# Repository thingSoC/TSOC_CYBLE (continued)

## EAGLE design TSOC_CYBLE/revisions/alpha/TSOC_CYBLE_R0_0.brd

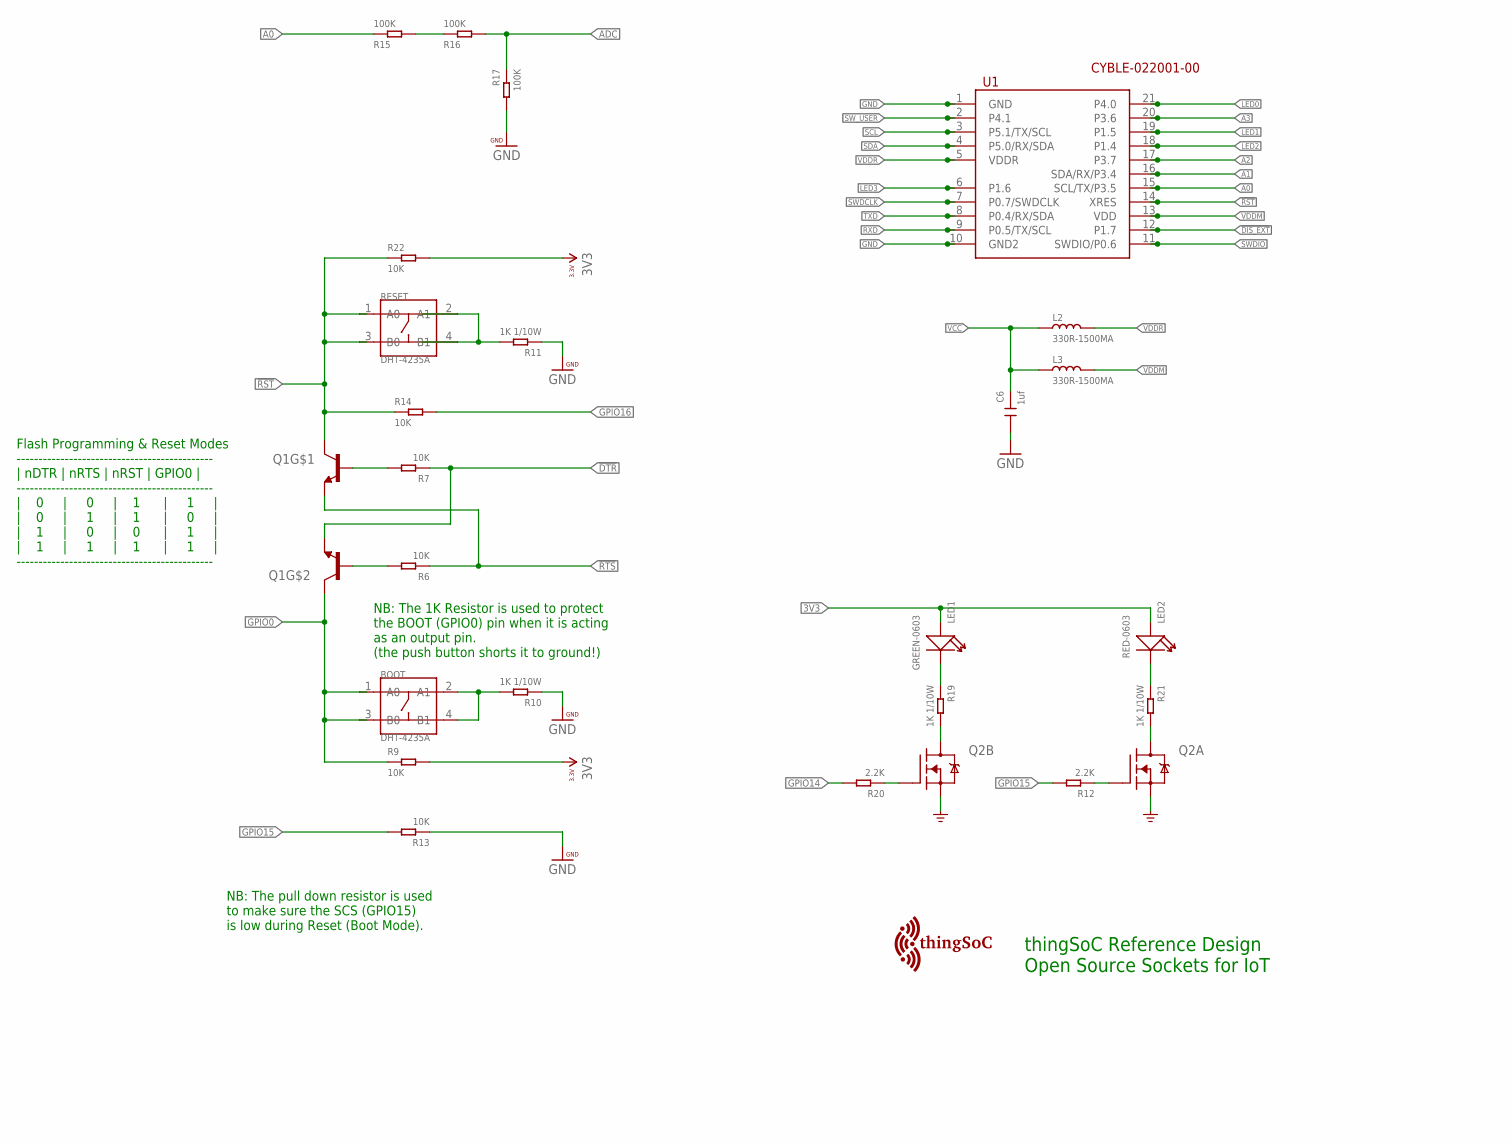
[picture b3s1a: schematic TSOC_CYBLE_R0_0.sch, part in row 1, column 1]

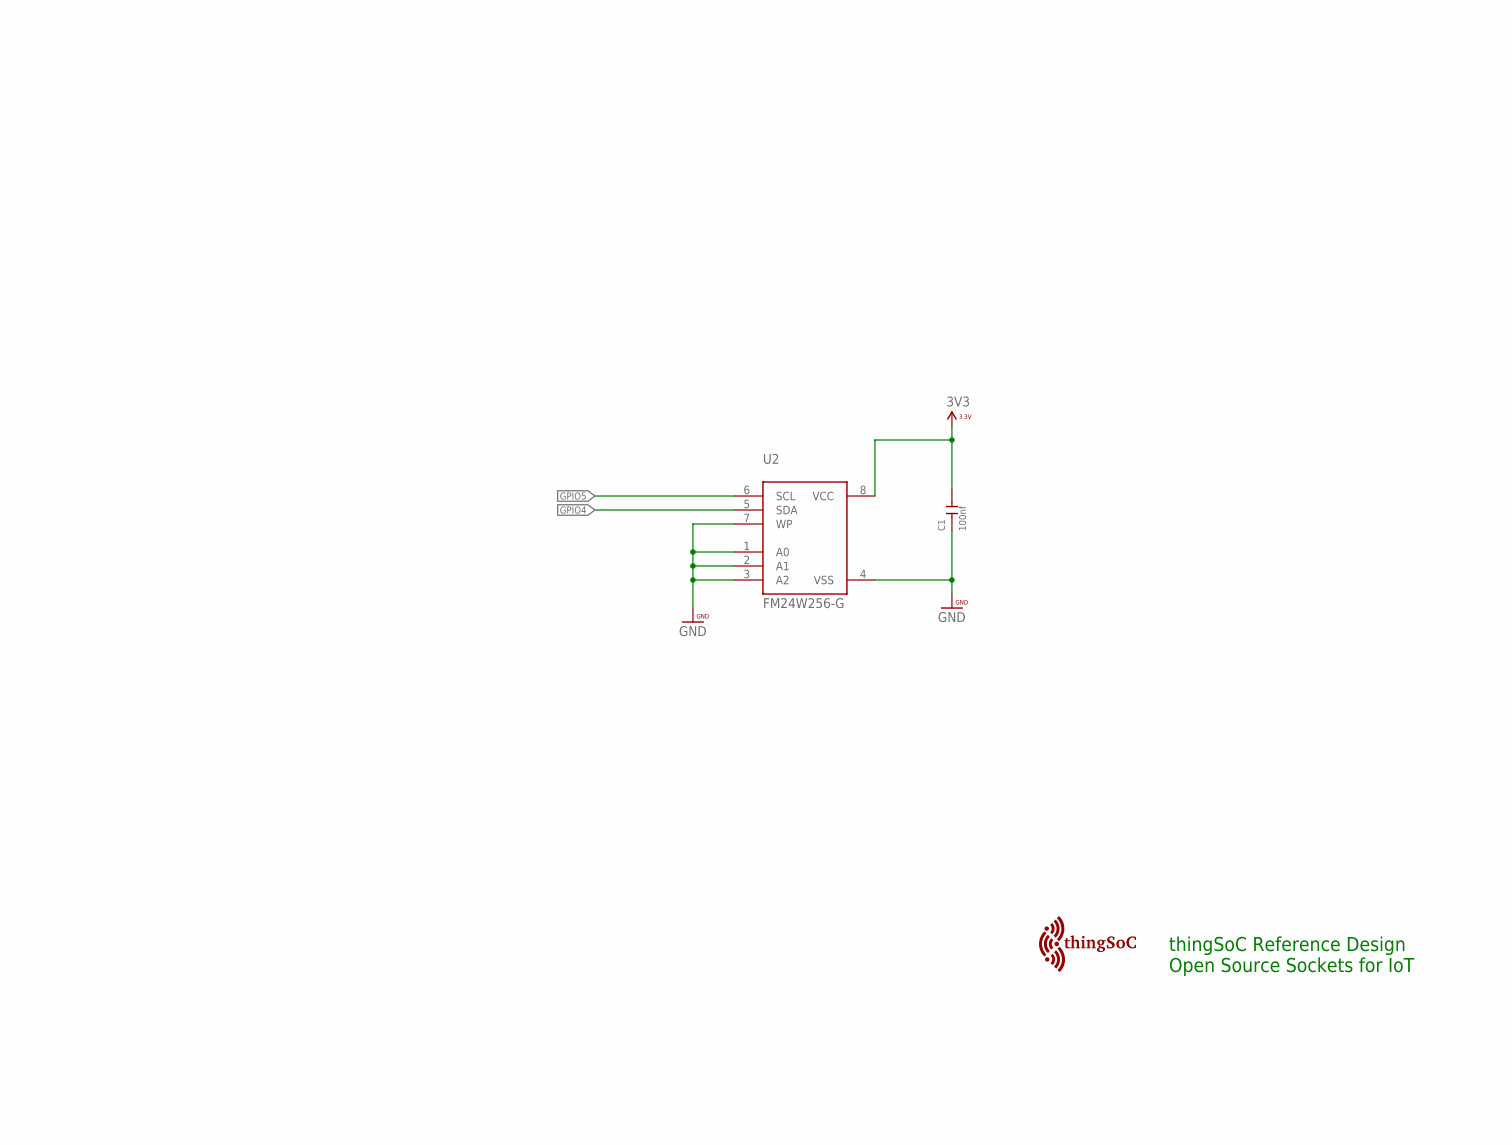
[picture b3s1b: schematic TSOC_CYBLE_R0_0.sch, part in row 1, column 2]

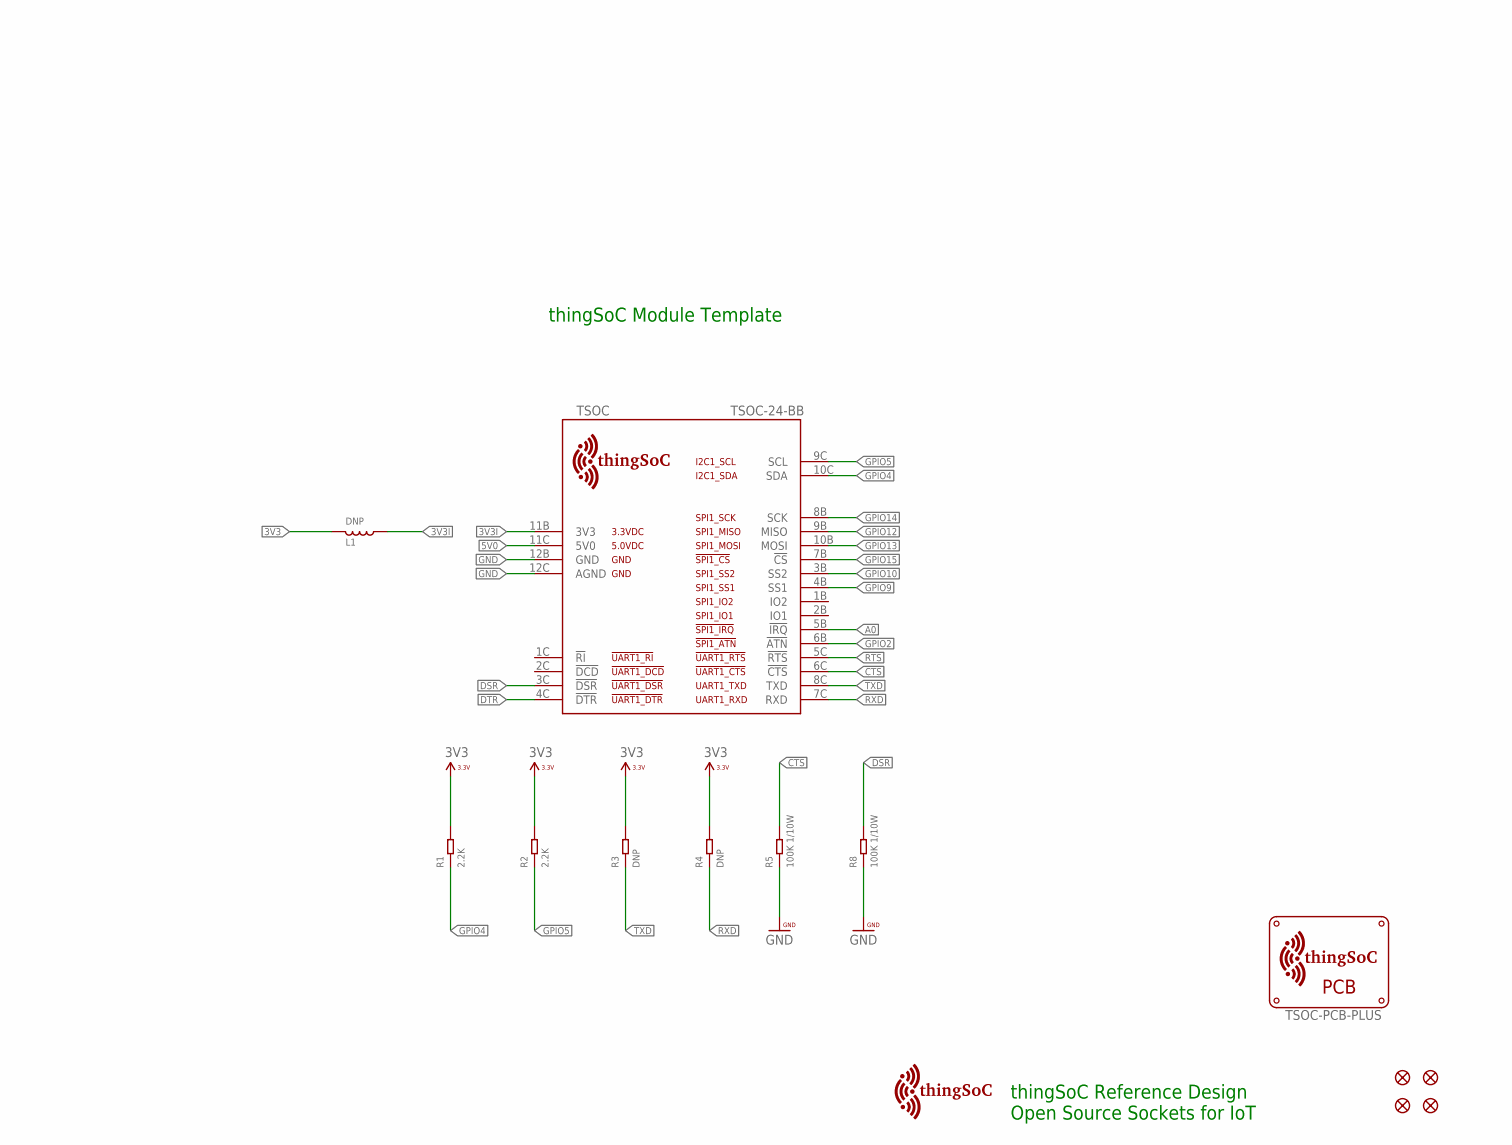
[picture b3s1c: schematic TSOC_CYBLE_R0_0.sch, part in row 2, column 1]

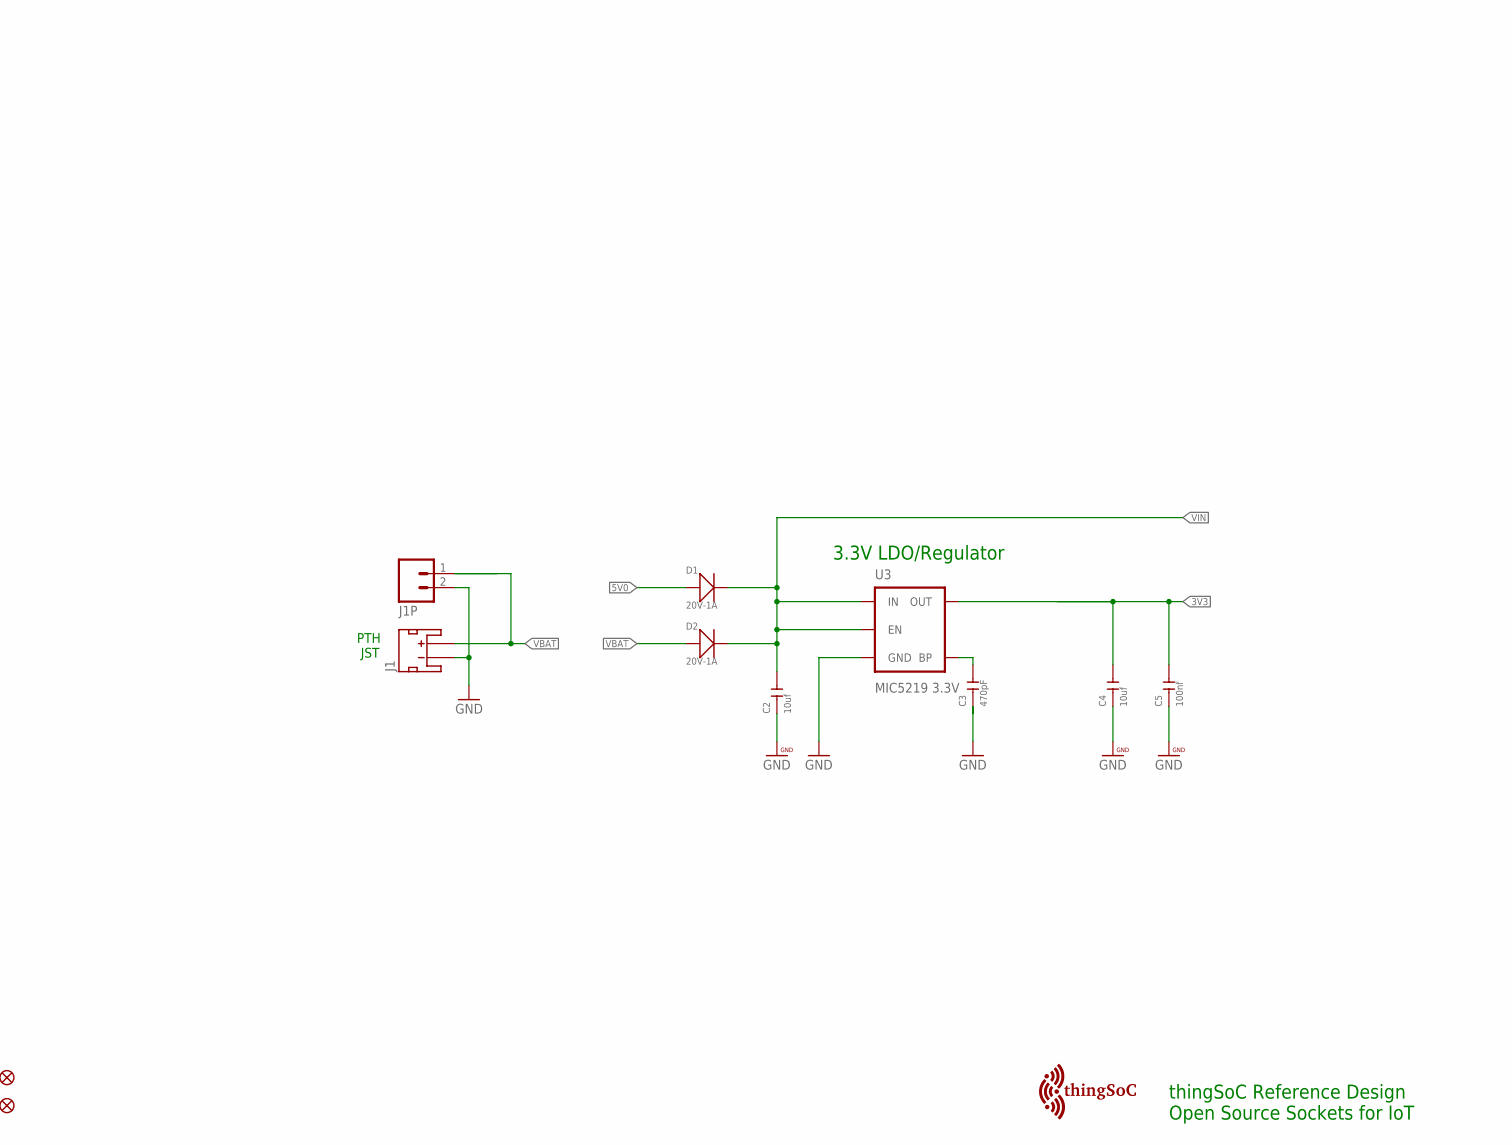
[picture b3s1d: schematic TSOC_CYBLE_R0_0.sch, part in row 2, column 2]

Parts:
$$U$1, $$U$2: TSOC-LOGO-MED
BOOT: DHT-4235A; SW4-SMD-4.2X3.2X2.5MM
C1, C5: 100nf; C0603
C2, C4: 10uf; C1206
C3: 470pF; C0603
C6: 1uf; C0603
D1, D2: 20V-1A; SOD-123
FID1, FID2, FID3, FID4: FIDUCIALUFIDUCIAL; MICRO-FIDUCIAL
J1: JST_2MM_MALE; JST-2-SMD
J1P: M02-JST-2-PTH-NO_SILK; JST-2-PTH-NS
L1: DNP; L0603
L2, L3: 330R-1500MA; L0805
LED1: GREEN-0603; LED-0603
LED2: RED-0603; LED-0603
PCB: TSOC-PCB-PLUS; TSOC-BB-BRD-PLUS-DIM
Q1: MMBT2222A; SOT363
Q2: FDG1024NZ; SOT95P280X110-6N
R1, R2, R12, R20: 2.2K; R0603
R3, R4: DNP; R0603
R5, R8: 100K 1/10W; R0603
R6, R7, R9, R13, R14, R22: 10K; R0603
R10, R11, R19, R21: 1K 1/10W; R0603
R15, R16, R17: 100K; R0603
RESET: DHT-4235A; SW4-SMD-4.2X3.2X2.5MM
TSOC: TSOC-24-BB; TSOC-BB-S24
U1: CYBLE-022001-00; PROC-BLE-10MM-21
U2: FM24W256-G; SO08
U3: MIC5219 3.3V; SOT23-5
U$101, U$102: TSOC-LOGO-MED

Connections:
3V3: C1.2, C4.2, C5.2, L1.1, LED1.+, LED2.+, R1.2, R2.2, R3.2, R4.2, R9.2, R22.2, U2.8 (VCC), U3.5 (OUT)
3V3I: L1.2, TSOC.11B (3V3)
5V0: D1.+, TSOC.11C (5V0)
!BOOTPD: BOOT.2 (A1), BOOT.4 (B1), R10.2
!CTS: R5.2, TSOC.6C (!CTS)
!DCDG: Q2.2 (G), R12.1
!DIS_EXT: U1.12 (P1.7)
!DSR: R8.2, TSOC.3C (!DSR)
!DTR: Q1.1 (E), R7.1, TSOC.4C (!DTR)
!RST: Q1.3 (C), R14.1, R22.1, RESET.1 (A0), RESET.3 (B0), U1.14 (XRES)
!RSTPD: R11.2, RESET.2 (A1), RESET.4 (B1)
!RTS: Q1.4 (E), R6.1, TSOC.5C (!RTS)
!SCSG: Q2.5 (G), R20.1
A0: R15.1, TSOC.5B (!IRQ), U1.15 (SCL/TX/P3.5)
A1: U1.16 (SDA/RX/P3.4)
A2: U1.17 (P3.7)
A3: U1.20 (P3.6)
ADC: R16.2, R17.1
ADC2: R15.2, R16.1
BYPASS1: C3.2, U3.4 (BP)
G0: Q2.6 (D), R21.2
G15: Q2.3 (D), R19.2
GND: C1.1, C2.1, C3.1, C4.1, C5.1, C6.2, J1.1 (-), J1P.2, Q2.1 (S), Q2.4 (S), R5.1, R8.1, R10.1, R11.1, R13.1, R17.2, TSOC.12B (GND), TSOC.12C (AGND), U1.1 (GND), U1.10 (GND2), U2.1 (A0), U2.2 (A1), U2.3 (A2), U2.4 (VSS), U2.7 (WP), U3.2 (GND)
GPIO0: BOOT.1 (A0), BOOT.3 (B0), Q1.6 (C), R9.1
GPIO2: TSOC.6B (!ATN)
GPIO4: R1.1, TSOC.10C (SDA), U2.5 (SDA)
GPIO5: R2.1, TSOC.9C (SCL), U2.6 (SCL)
GPIO9: TSOC.4B (SS1)
GPIO10: TSOC.3B (SS2)
GPIO12: TSOC.9B (MISO)
GPIO13: TSOC.10B (MOSI)
GPIO14: R20.2, TSOC.8B (SCK)
GPIO15: R12.2, R13.2, TSOC.7B (!CS)
GPIO16: R14.2
LED0: U1.21 (P4.0)
LED1: LED1.-, R19.1, U1.19 (P1.5)
LED2: LED2.-, R21.1, U1.18 (P1.4)
LED3: U1.6 (P1.6)
RES: Q1.5 (B), R7.2
ROS: Q1.2 (B), R6.2
RXD: R4.1, TSOC.7C (RXD), U1.9 (P0.5/TX/SCL)
SCL: U1.3 (P5.1/TX/SCL)
SDA: U1.4 (P5.0/RX/SDA)
SWDCLK: U1.7 (P0.7/SWDCLK)
SWDIO: U1.11 (SWDIO/P0.6)
SW_USER: U1.2 (P4.1)
TXD: R3.1, TSOC.8C (TXD), U1.8 (P0.4/RX/SDA)
VBAT: D2.+, J1.2 (+), J1P.1
VCC: C6.1, L2.1, L3.1
VDDM: L3.2, U1.13 (VDD)
VDDR: L2.2, U1.5 (VDDR)
VIN: C2.2, D1.-, D2.-, U3.1 (IN), U3.3 (EN)

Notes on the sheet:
thingSoC Reference Design Open Source Sockets for IoT
thingSoC Module Template
Flash Programming & Reset Modes --------------------------------------------- | nDTR | nRTS | nRST | GPIO0 | --------------------------------------------- | 0 | 0 | 1 | 1 | | 0 | 1 | 1 | 0 | | 1 | 0 | 0 | 1 | | 1 | 1 | 1 | 1 | ---------------------------------------------
NB: The 1K Resistor is used to protect the BOOT (GPIO0) pin when it is acting as an output pin. (the push button shorts it to ground!)
NB: The pull down resistor is used to make sure the SCS (GPIO15) is low during Reset (Boot Mode).
PTH JST
3.3V LDO/Regulator

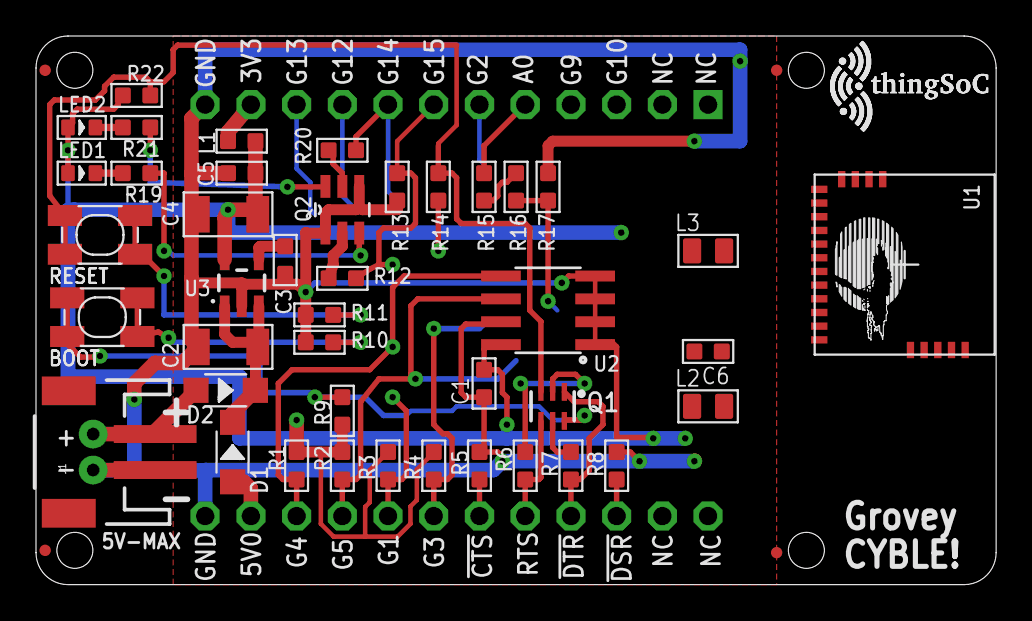
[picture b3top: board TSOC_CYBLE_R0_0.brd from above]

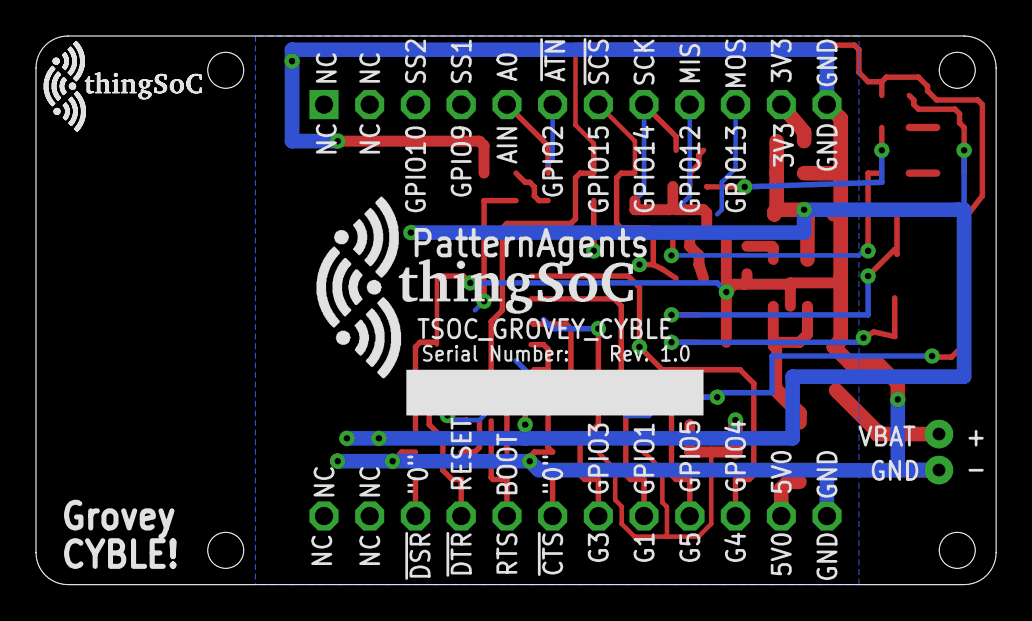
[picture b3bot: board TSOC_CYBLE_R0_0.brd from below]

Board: 2 copper layers, 53.3 x 30.5 mm, 54 parts (4 on the bottom side), 35 nets.

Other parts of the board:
U$100: TSOC-LOGO-LRG

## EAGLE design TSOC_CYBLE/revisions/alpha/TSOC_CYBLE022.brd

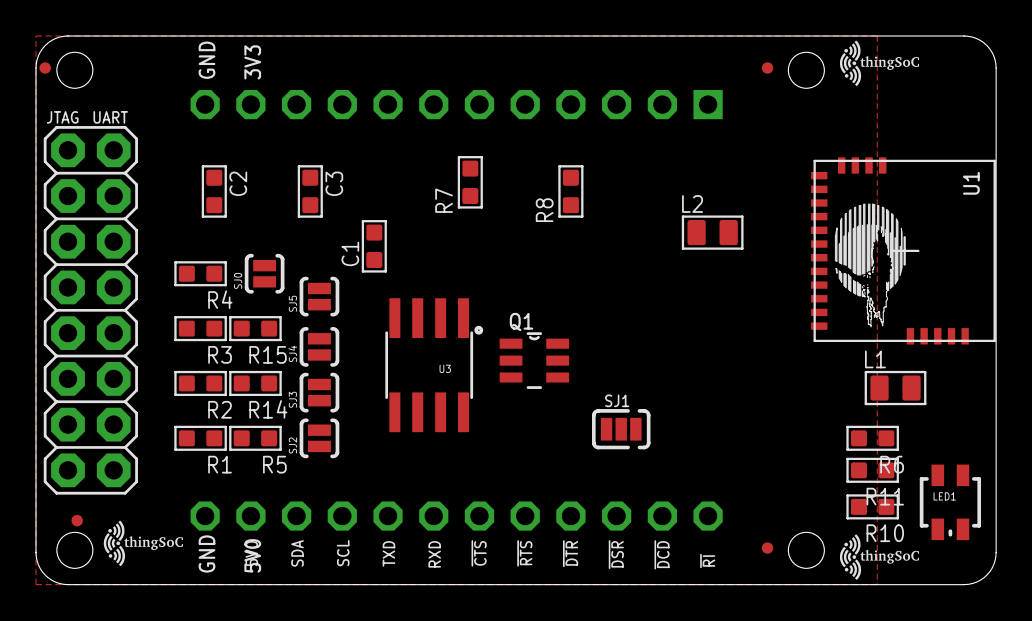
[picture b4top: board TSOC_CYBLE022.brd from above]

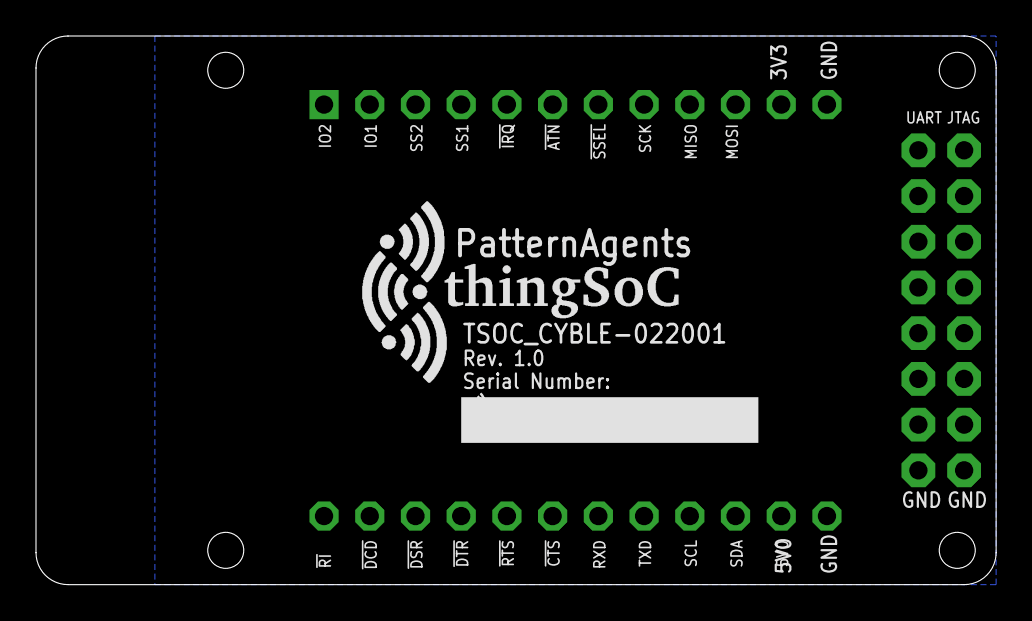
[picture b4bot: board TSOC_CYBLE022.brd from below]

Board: 2 copper layers, 53.3 x 30.5 mm, 39 parts (2 on the bottom side), 26 nets, no tracks yet.

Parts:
$$U$1, $$U$3, $$U$4: TSOC-LOGO-SMALL; TSOC-LOGO-SML
C1: 1uf; C0603
C2, C3: 100nf; C0603
FID1, FID2, FID3, FID4: FIDUCIALUFIDUCIAL; MICRO-FIDUCIAL
J3: 2X8
L1, L2: 330R-1500MA; L0805
LED1: LED-TRICOLOR; LED-TRICOLOR-SMD
Q1: FDC6420C; SOT95P280X110-6N
R1, R2, R3, R4, R5, R7, R8: 10K; R0603
R6, R10, R11: 1K; R0603
R14, R15: 2.2K; R0603
SJ0, SJ2, SJ3, SJ4, SJ5: JMP-2-NO
SJ1: JMP-3-NC
TSOC: TSOC-24-BB; TSOC-BB-S24
U1: CYBLE-022001-00; PROC-BLE-10MM-21
U3: FM24W256-G; SO08
U$1: TSOC-PCB-PLUS; TSOC-BB-BRD-PLUS-DIM
U$100: TSOC-LOGO-SMALL; TSOC-LOGO-SML
U$101: TSOC-LOGO-LRG

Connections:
3V3: SJ1.1, TSOC.11B
5V0: SJ1.3, TSOC.11C
!CTS: J3.14, TSOC.6C
!DTR: J3.6, TSOC.4C
!RST: C3.1, J3.5, R5.1, SJ5.1, U1.14
!RTS: J3.4, TSOC.5C
A0: R1.1, SJ0.2, U1.15, U3.1
A1: R2.1, SJ2.2, U1.16, U3.2
A2: R3.1, SJ3.2, U1.17, U3.3
BLU: LED1.B, R6.2
GATE: Q1.3, Q1.6, R7.1
GND: C1.2, C2.2, C3.2, J3.15, J3.16, Q1.5, R8.1, SJ0.1, SJ2.1, SJ3.1, SJ4.1, TSOC.12B, TSOC.12C, U1.1, U1.10, U3.4
GRN: LED1.G, R11.2
PWR_UP: Q1.1, R8.2
RED: LED1.R, R10.2
RXD: J3.10, TSOC.7C, U1.9
SCL: J3.3, R15.1, TSOC.9C, U1.3, U3.6
SDA: J3.13, R14.1, TSOC.10C, U1.4, U3.5
SWDCLK: J3.7, U1.7
SWDIO: J3.9, U1.11
TXD: J3.8, TSOC.8C, U1.8
VCC: C1.1, J3.11, J3.12, L1.1, L2.1, Q1.2, R7.2, SJ1.2
VCC_PU: C2.1, LED1.A, Q1.4, R1.2, R2.2, R3.2, R4.2, R5.2, R14.2, R15.2, U3.8
VDDM: L2.2, U1.13
VDDR: L1.2, U1.5
WP: R4.1, SJ4.2, U3.7

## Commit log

2016-09-03 initial version
2016-09-04 update images
